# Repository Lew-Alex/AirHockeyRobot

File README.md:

# Air Hockey Robot

A robotic air-hockey table. A camera tracks the puck, a policy trained in
simulation decides where the mallet should go, and an ESP32 drives two brushed
DC motors through off-board motor drivers.

This is a personal project in progress. The status table below separates what
exists in this repository from what is only planned.

## Status

| Area | Status |
|---|---|
| Puck tracker (webcam, HSV yellow mask) | Prototype works on a webcam. No table calibration, filtering or bounce handling yet. |
| Android App Perception Test | High-speed recorder with an integrated Python tracking toggle, live green overlay and local TCP XY output on port 8765. APK build and on-device validation pending; see `src/AndroidApp/README.md`. |
| Camera latency test (OpenCV) | Script exists. Results are not recorded in this repo. |
| iPhone 120 fps camera test app | Source written (`src/iphone_camera_test`), **not yet compiled or run**: Xcode is not installed on the development Mac. |
| Simulation (Pygame) | Physics, scripted opponent and reward shaping exist. |
| PPO training | Actor and critic exist. The trainer collects a short rollout only. GAE, the PPO update and the training loop are not written. |
| Breakout PCB (ESP32 DevKitC V4) | Designed and passes Prometheus checks and KiCad DRC. **Not ordered, assembled or tested.** |
| Motor drivers, power supply | Candidates only. Nothing is decided (see `docs/hardware.md`). |
| ESP32 firmware | Not started. |
| ROS 2 integration | Not started. |

## Repository layout

```text
.
├── README.md
├── CLAUDE.md                      Project notes for AI coding assistants
├── docs/                          Architecture, hardware, PCB, perception, training plan
├── .claude/skills/                Project skills (PCB build, PPO training, iPhone app)
└── src/
    ├── AI_SIm/                    Pygame simulation and PPO code
    ├── perception/
    │   ├── prototype/             Webcam yellow-puck tracker
    │   └── input_testing/         Camera latency test script
    ├── test_pcb/                  Breakout PCB (Prometheus) and fabrication outputs
    └── iphone_camera_test/        iOS app to test 120 fps at a fixed shutter speed
```

## System overview

```text
camera ──> Mac ──(USB serial)──> ESP32 ──PWM/DIR──> motor drivers ──> 2 × 775 motors
 (puck)   tracking, filter,        │                     ^
          policy                   └── encoders, limit switches, e-stop sense
```

The Mac is meant to run perception and the trained policy. The ESP32 handles the
low-level motor interface through the breakout PCB. See `docs/architecture.md`.

## Quick start

Run each command from the folder named in front of it.

**Puck tracker** (`src/perception/prototype`)

```bash
python3 -m venv .venv && source .venv/bin/activate
python3 -m pip install -r requirements.txt
python3 puck_tracker.py                 # add --camera 1 if the wrong camera opens
python3 -m unittest discover -s tests
```

**Camera latency test** (repository root, using the tracker's environment)

```bash
src/perception/prototype/.venv/bin/python src/perception/input_testing/camera_latency.py
```

**Simulation** (`src/AI_SIm`, needs `pip install -r requirements.txt`)

```bash
python3 simulation.py                   # Pygame demo: N switches mode, M is manual, Space resets
python3 ppo_trainer.py                  # short rollout, prints rewards and advantages
```

Torch 2.0.x prints a "Failed to initialize NumPy" warning when NumPy 2 is installed.
It is harmless here; upgrade torch or use `numpy<2` to remove it.

**PCB** (`src/test_pcb`). Prometheus needs Java 17+; FreeRouting 2.0.1 needs
Java 21. If only Java 17 is installed, point `PROMETHEUS_JAVA` at a Java 21
runtime first.

```bash
prometheus board.py out/ --spec req.json --json
python3 tools/verify_nets.py            # checks the generated netlists against board.py
```

**iPhone app** (`src/iphone_camera_test`): see its README. It needs Xcode.

## Documentation

- `docs/architecture.md`: components and data flow
- `docs/hardware.md`: parts in hand, candidates and open decisions
- `docs/pcb.md`: connector and pin map, assembly and bring-up checklist
- `docs/perception.md`: camera plan, filtering and what the policy receives
- `docs/training-plan.md`: PPO status and the remaining steps

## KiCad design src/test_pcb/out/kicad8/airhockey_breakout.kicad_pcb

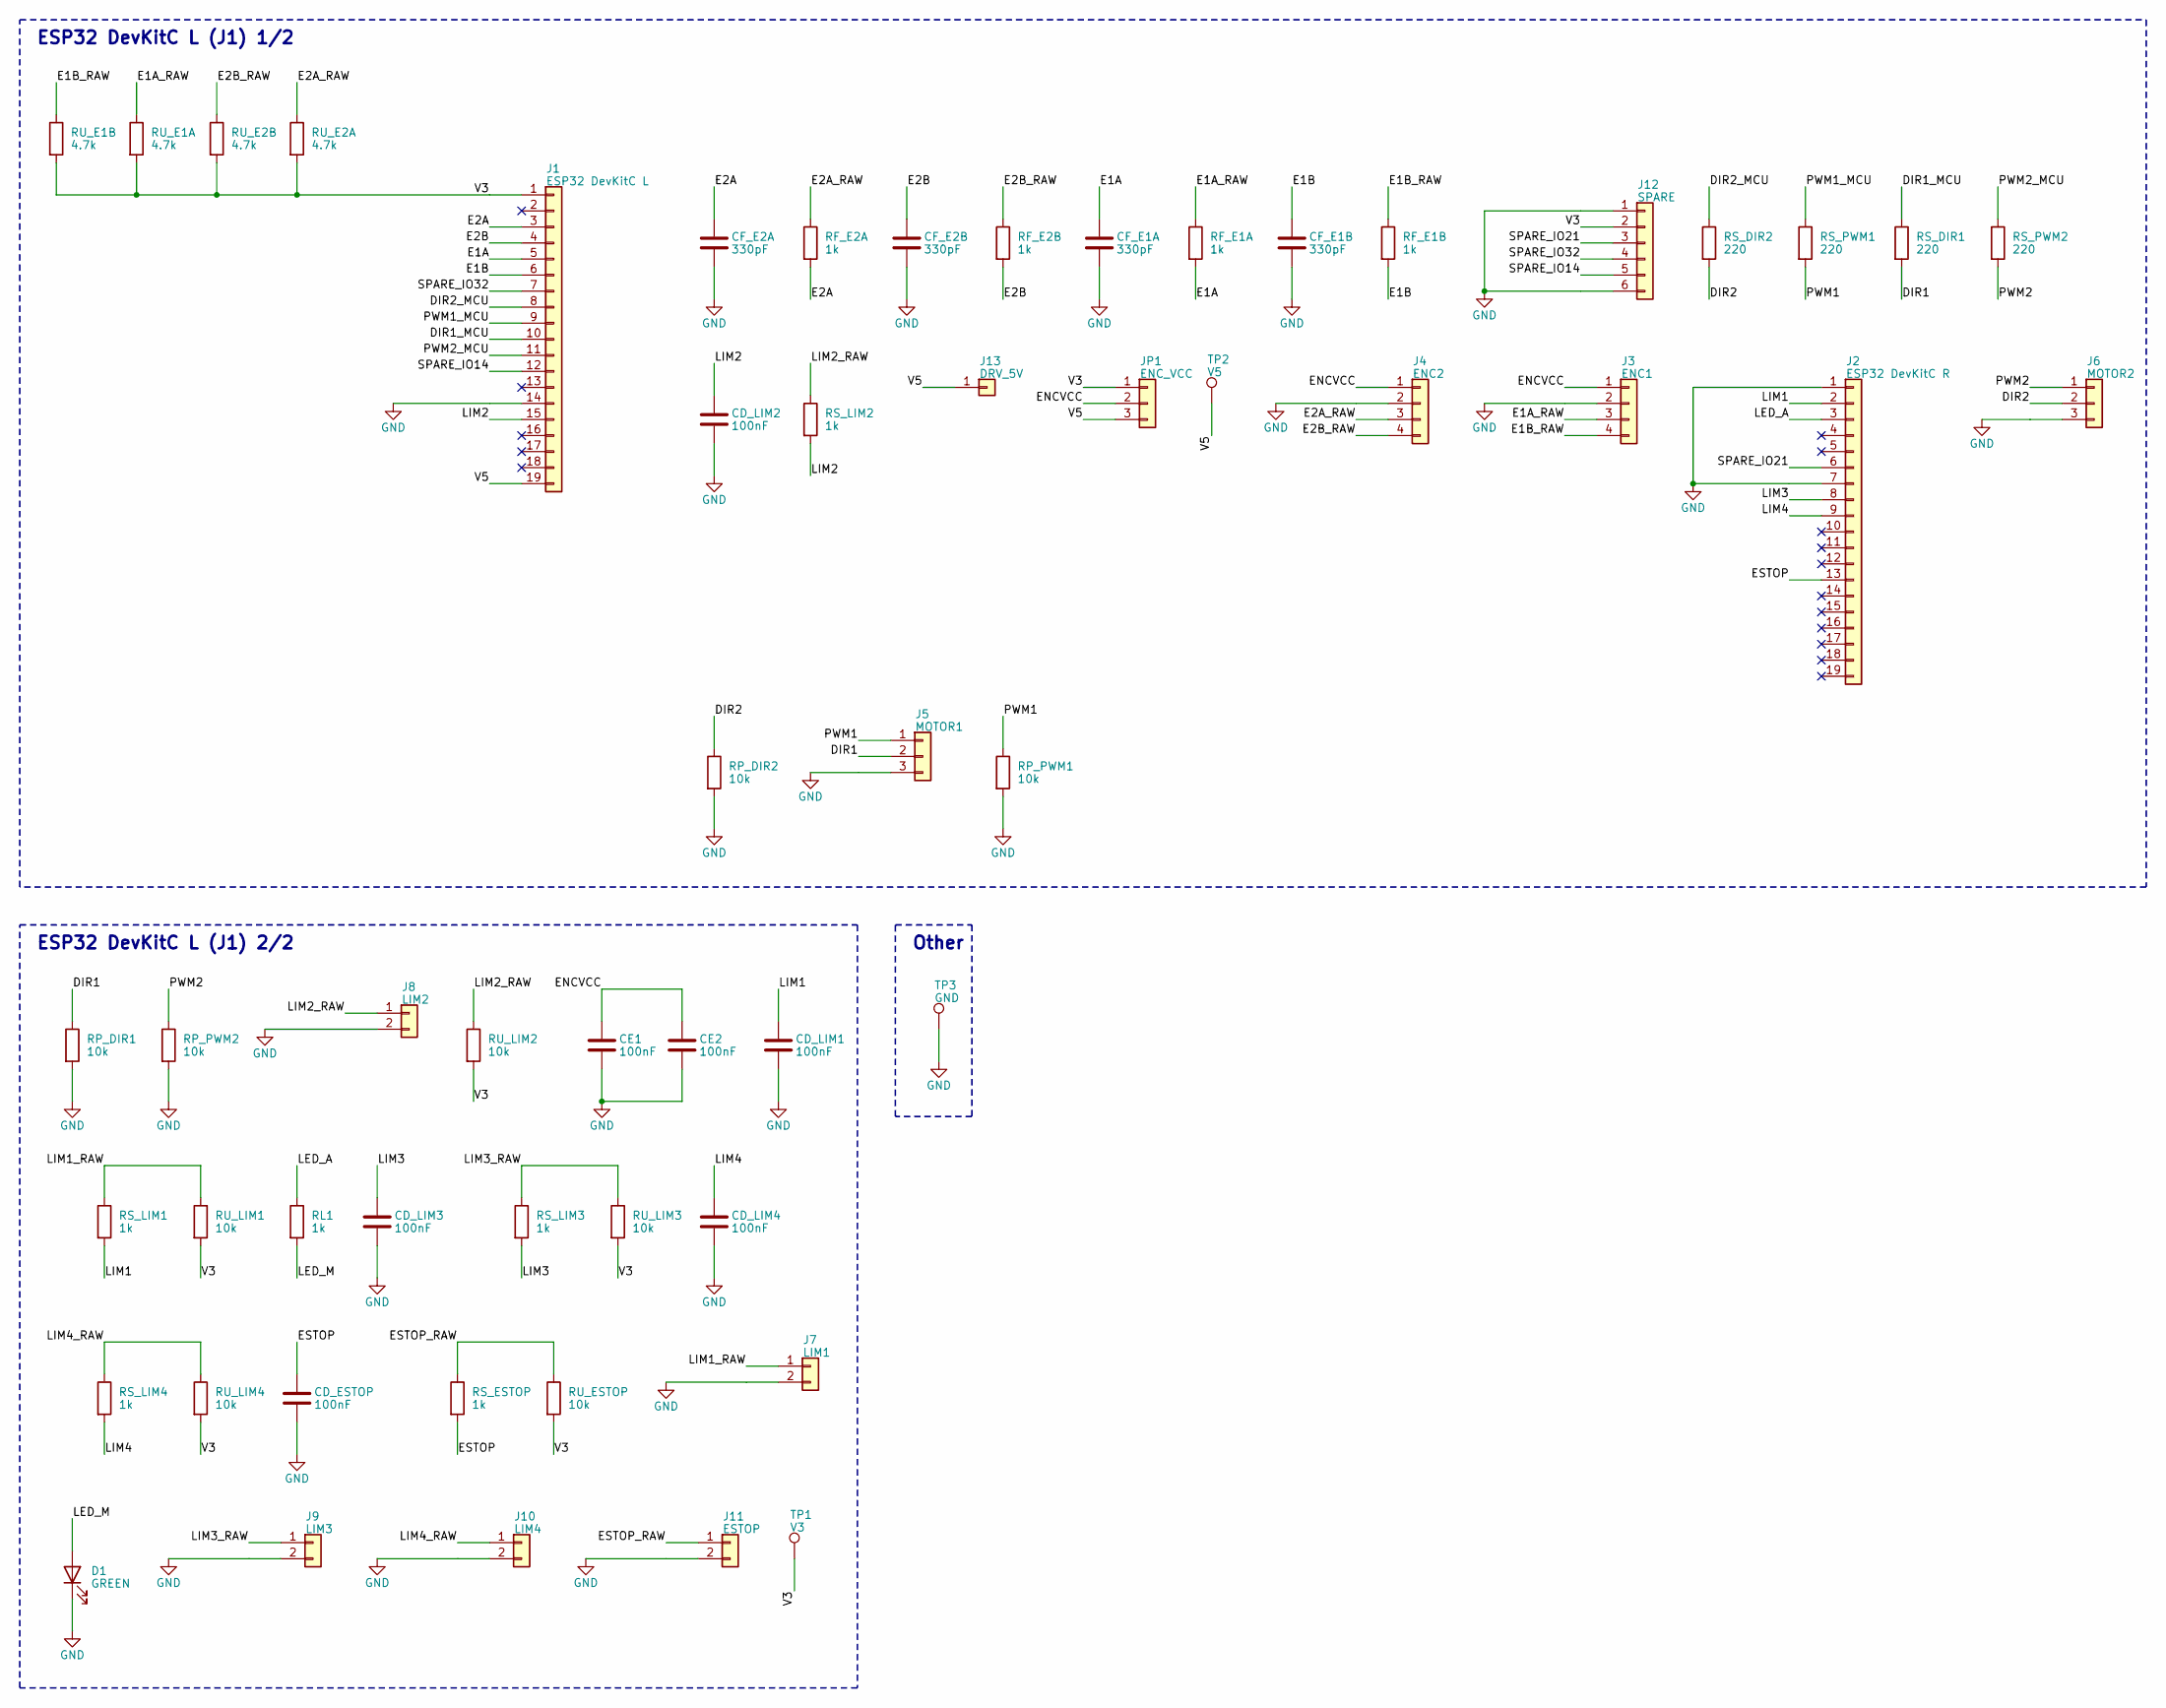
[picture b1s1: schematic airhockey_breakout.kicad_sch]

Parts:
CD_ESTOP: 100nF; C_Disc_D3.0mm_W2.0mm_P2.50mm
CD_LIM1, CD_LIM2, CD_LIM3, CD_LIM4: 100nF; C_Disc_D3.0mm_W2.0mm_P2.50mm
CE1, CE2: 100nF; C_Disc_D3.0mm_W2.0mm_P2.50mm
CF_E1A, CF_E1B, CF_E2A, CF_E2B: 330pF; C_Disc_D3.0mm_W2.0mm_P2.50mm
D1: GREEN; LED_D3.0mm
J1: ESP32 DevKitC L; PinSocket_1x19_P2.54mm_Vertical
J2: ESP32 DevKitC R; PinSocket_1x19_P2.54mm_Vertical
J3: ENC1; JST_XH_B4B-XH-A_1x04_P2.50mm_Vertical
J4: ENC2; JST_XH_B4B-XH-A_1x04_P2.50mm_Vertical
J5: MOTOR1; JST_XH_B3B-XH-A_1x03_P2.50mm_Vertical
J6: MOTOR2; JST_XH_B3B-XH-A_1x03_P2.50mm_Vertical
J7: LIM1; JST_XH_B2B-XH-A_1x02_P2.50mm_Vertical
J8: LIM2; JST_XH_B2B-XH-A_1x02_P2.50mm_Vertical
J9: LIM3; JST_XH_B2B-XH-A_1x02_P2.50mm_Vertical
J10: LIM4; JST_XH_B2B-XH-A_1x02_P2.50mm_Vertical
J11: ESTOP; JST_XH_B2B-XH-A_1x02_P2.50mm_Vertical
J12: SPARE; PinHeader_1x06_P2.54mm_Vertical; LCSC C37208
J13: DRV_5V; PinSocket_1x01_P2.54mm_Vertical
JP1: ENC_VCC; PinHeader_1x03_P2.54mm_Vertical; LCSC C49257
RF_E1A, RF_E1B, RF_E2A, RF_E2B: 1k; R_Axial_DIN0207_L6.3mm_D2.5mm_P7.62mm_Horizontal
RL1: 1k; R_Axial_DIN0207_L6.3mm_D2.5mm_P7.62mm_Horizontal
RP_DIR1, RP_DIR2: 10k; R_Axial_DIN0207_L6.3mm_D2.5mm_P7.62mm_Horizontal
RP_PWM1, RP_PWM2: 10k; R_Axial_DIN0207_L6.3mm_D2.5mm_P7.62mm_Horizontal
RS_DIR1, RS_DIR2: 220; R_Axial_DIN0207_L6.3mm_D2.5mm_P7.62mm_Horizontal
RS_ESTOP: 1k; R_Axial_DIN0207_L6.3mm_D2.5mm_P7.62mm_Horizontal
RS_LIM1, RS_LIM2, RS_LIM3, RS_LIM4: 1k; R_Axial_DIN0207_L6.3mm_D2.5mm_P7.62mm_Horizontal
RS_PWM1, RS_PWM2: 220; R_Axial_DIN0207_L6.3mm_D2.5mm_P7.62mm_Horizontal
RU_E1A, RU_E1B, RU_E2A, RU_E2B: 4.7k; R_Axial_DIN0207_L6.3mm_D2.5mm_P7.62mm_Horizontal
RU_ESTOP: 10k; R_Axial_DIN0207_L6.3mm_D2.5mm_P7.62mm_Horizontal
RU_LIM1, RU_LIM2, RU_LIM3, RU_LIM4: 10k; R_Axial_DIN0207_L6.3mm_D2.5mm_P7.62mm_Horizontal
TP1: V3; TestPoint_THTPad_D2.0mm_Drill1.0mm
TP2: V5; TestPoint_THTPad_D2.0mm_Drill1.0mm
TP3: GND; TestPoint_THTPad_D2.0mm_Drill1.0mm

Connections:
DIR1: J5.2, RP_DIR1.1, RS_DIR1.2
DIR1_MCU: J1.10, RS_DIR1.1
DIR2: J6.2, RP_DIR2.1, RS_DIR2.2
DIR2_MCU: J1.8, RS_DIR2.1
E1A: CF_E1A.1, J1.5, RF_E1A.2
E1A_RAW: J3.3, RF_E1A.1, RU_E1A.1
E1B: CF_E1B.1, J1.6, RF_E1B.2
E1B_RAW: J3.4, RF_E1B.1, RU_E1B.1
E2A: CF_E2A.1, J1.3, RF_E2A.2
E2A_RAW: J4.3, RF_E2A.1, RU_E2A.1
E2B: CF_E2B.1, J1.4, RF_E2B.2
E2B_RAW: J4.4, RF_E2B.1, RU_E2B.1
ENCVCC: CE1.1, CE2.1, J3.1, J4.1, JP1.2
ESTOP: CD_ESTOP.1, J2.13, RS_ESTOP.2
ESTOP_RAW: J11.1, RS_ESTOP.1, RU_ESTOP.1
GND: CD_ESTOP.2, CD_LIM1.2, CD_LIM2.2, CD_LIM3.2, CD_LIM4.2, CE1.2, CE2.2, CF_E1A.2, CF_E1B.2, CF_E2A.2, CF_E2B.2, D1.1 (K), J1.14, J2.1, J2.7, J3.2, J4.2, J5.3, J6.3, J7.2, J8.2, J9.2, J10.2, J11.2, J12.1, J12.6, RP_DIR1.2, RP_DIR2.2, RP_PWM1.2, RP_PWM2.2, TP3.1
LED_A: J2.3, RL1.1
LED_M: D1.2 (A), RL1.2
LIM1: CD_LIM1.1, J2.2, RS_LIM1.2
LIM1_RAW: J7.1, RS_LIM1.1, RU_LIM1.1
LIM2: CD_LIM2.1, J1.15, RS_LIM2.2
LIM2_RAW: J8.1, RS_LIM2.1, RU_LIM2.1
LIM3: CD_LIM3.1, J2.8, RS_LIM3.2
LIM3_RAW: J9.1, RS_LIM3.1, RU_LIM3.1
LIM4: CD_LIM4.1, J2.9, RS_LIM4.2
LIM4_RAW: J10.1, RS_LIM4.1, RU_LIM4.1
PWM1: J5.1, RP_PWM1.1, RS_PWM1.2
PWM1_MCU: J1.9, RS_PWM1.1
PWM2: J6.1, RP_PWM2.1, RS_PWM2.2
PWM2_MCU: J1.11, RS_PWM2.1
SPARE_IO14: J1.12, J12.5
SPARE_IO21: J2.6, J12.3
SPARE_IO32: J1.7, J12.4
V3: J1.1, J12.2, JP1.1, RU_E1A.2, RU_E1B.2, RU_E2A.2, RU_E2B.2, RU_ESTOP.2, RU_LIM1.2, RU_LIM2.2, RU_LIM3.2, RU_LIM4.2, TP1.1
V5: J1.19, J13.1, JP1.3, TP2.1

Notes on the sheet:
ESP32 DevKitC L (J1) 1/2
ESP32 DevKitC L (J1) 2/2
Other

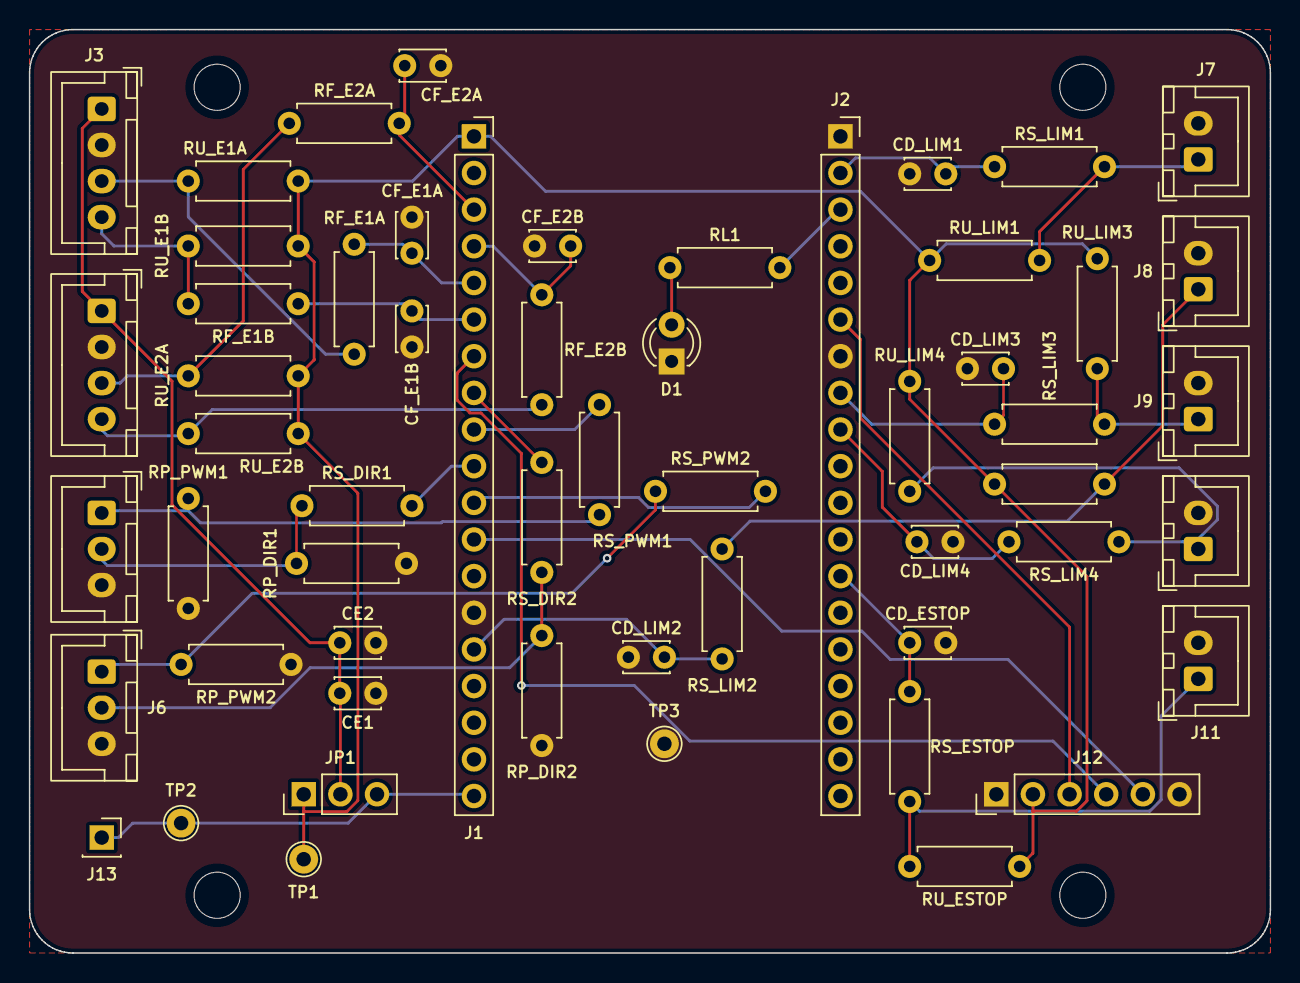
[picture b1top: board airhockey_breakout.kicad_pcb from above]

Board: 2 copper layers, 86.0 x 64.0 mm, 60 parts (0 on the bottom side), 35 nets.

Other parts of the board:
H1, H2, H3, H4: hole 3.2 mm; MountingHole_3.2mm

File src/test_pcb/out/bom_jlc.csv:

Comment,Designator,Footprint,LCSC Part #
100nF,"CD_ESTOP,CD_LIM1,CD_LIM2,CD_LIM3,CD_LIM4,CE1,CE2",C_Disc_D3.0mm_W2.0mm_P2.50mm,
330pF,"CF_E1A,CF_E2A,CF_E1B,CF_E2B",C_Disc_D3.0mm_W2.0mm_P2.50mm,
GREEN,D1,LED_D3.0mm,
ESP32 DevKitC L,J1,PinSocket_1x19_P2.54mm_Vertical,
LIM4,J10,JST_XH_B2B-XH-A_1x02_P2.50mm_Vertical,
ESTOP,J11,JST_XH_B2B-XH-A_1x02_P2.50mm_Vertical,
SPARE,J12,PinHeader_1x06_P2.54mm_Vertical,C37208
DRV_5V,J13,PinSocket_1x01_P2.54mm_Vertical,
ESP32 DevKitC R,J2,PinSocket_1x19_P2.54mm_Vertical,
ENC1,J3,JST_XH_B4B-XH-A_1x04_P2.50mm_Vertical,
ENC2,J4,JST_XH_B4B-XH-A_1x04_P2.50mm_Vertical,
MOTOR1,J5,JST_XH_B3B-XH-A_1x03_P2.50mm_Vertical,
MOTOR2,J6,JST_XH_B3B-XH-A_1x03_P2.50mm_Vertical,
LIM1,J7,JST_XH_B2B-XH-A_1x02_P2.50mm_Vertical,
LIM2,J8,JST_XH_B2B-XH-A_1x02_P2.50mm_Vertical,
LIM3,J9,JST_XH_B2B-XH-A_1x02_P2.50mm_Vertical,
ENC_VCC,JP1,PinHeader_1x03_P2.54mm_Vertical,C49257
1k,"RF_E1A,RF_E2A,RF_E1B,RF_E2B,RL1,RS_ESTOP,RS_LIM1,RS_LIM2,RS_LIM3,RS_LIM4",R_Axial_DIN0207_L6.3mm_D2.5mm_P7.62mm_Horizontal,
10k,"RP_DIR1,RP_DIR2,RP_PWM1,RP_PWM2,RU_ESTOP,RU_LIM1,RU_LIM2,RU_LIM3,RU_LIM4",R_Axial_DIN0207_L6.3mm_D2.5mm_P7.62mm_Horizontal,
220,"RS_DIR1,RS_DIR2,RS_PWM1,RS_PWM2",R_Axial_DIN0207_L6.3mm_D2.5mm_P7.62mm_Horizontal,
4.7k,"RU_E1A,RU_E2A,RU_E1B,RU_E2B",R_Axial_DIN0207_L6.3mm_D2.5mm_P7.62mm_Horizontal,
V3,TP1,TestPoint_THTPad_D2.0mm_Drill1.0mm,
V5,TP2,TestPoint_THTPad_D2.0mm_Drill1.0mm,
GND,TP3,TestPoint_THTPad_D2.0mm_Drill1.0mm,
